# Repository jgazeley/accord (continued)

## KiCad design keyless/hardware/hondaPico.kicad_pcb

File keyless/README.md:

# Accord keyless

Pico W firmware and hardware for the keyless-entry module in a 2001 Honda
Accord. It provides BLE commands, proximity-based lock/unlock, automatic
relocking, and control of the trunk, lights and horn. It runs locally on the
board and retains USB/serial interfaces for diagnostics and control.

## Hardware

Open [hardware/hondaPico.kicad_pro](hardware/hondaPico.kicad_pro) in KiCad 9.
Install KiCad's standard symbol, footprint and 3D-model libraries. Project-local
custom symbols and footprints are included. The hardware project retains its
original `hondaPico` filename.

KiCad CLI 9.0.2 loads and exports the schematic and PCB. Checks report no errors,
but there are two schematic warnings, three board warnings and eight
PCB/schematic parity warnings. These include a missing J2 footprint and differing
R14/R15 values. See the [validation report](validation/kicad-20261027/README.md)
before using the design for fabrication. The 3D appearance has not been verified.

## Build

Use Arduino CLI 1.4.1 with Earle Philhower's Arduino-Pico core 6.1.0.
From `keyless/`:

```sh
arduino-cli compile --fqbn rp2040:rp2040:rpipicow:ipbtstack=ipv4btcble --build-path /tmp/accord-keyless-build firmware/accord-keyless
```

The board option enables BLE. The sketch is
[accord-keyless.ino](firmware/accord-keyless/accord-keyless.ino); it does not
require a Wi-Fi credential header. The existing BLE advertised name and
protocol names are unchanged.

## Tests

From `keyless/`, compile and run each native test:

```sh
for test in interlock relock proximity_act; do
  cc -std=c11 -Wall -Wextra -Werror "tests/${test}_test.c" -o "/tmp/accord-keyless-${test}" || exit
  "/tmp/accord-keyless-${test}" || exit
done
```

All three tests pass. The interlock and relock tests exercise copies of firmware
logic; they do not replace board testing or in-car proximity calibration.

Source provenance and validation are recorded in
[SOURCE_MANIFEST.json](SOURCE_MANIFEST.json).

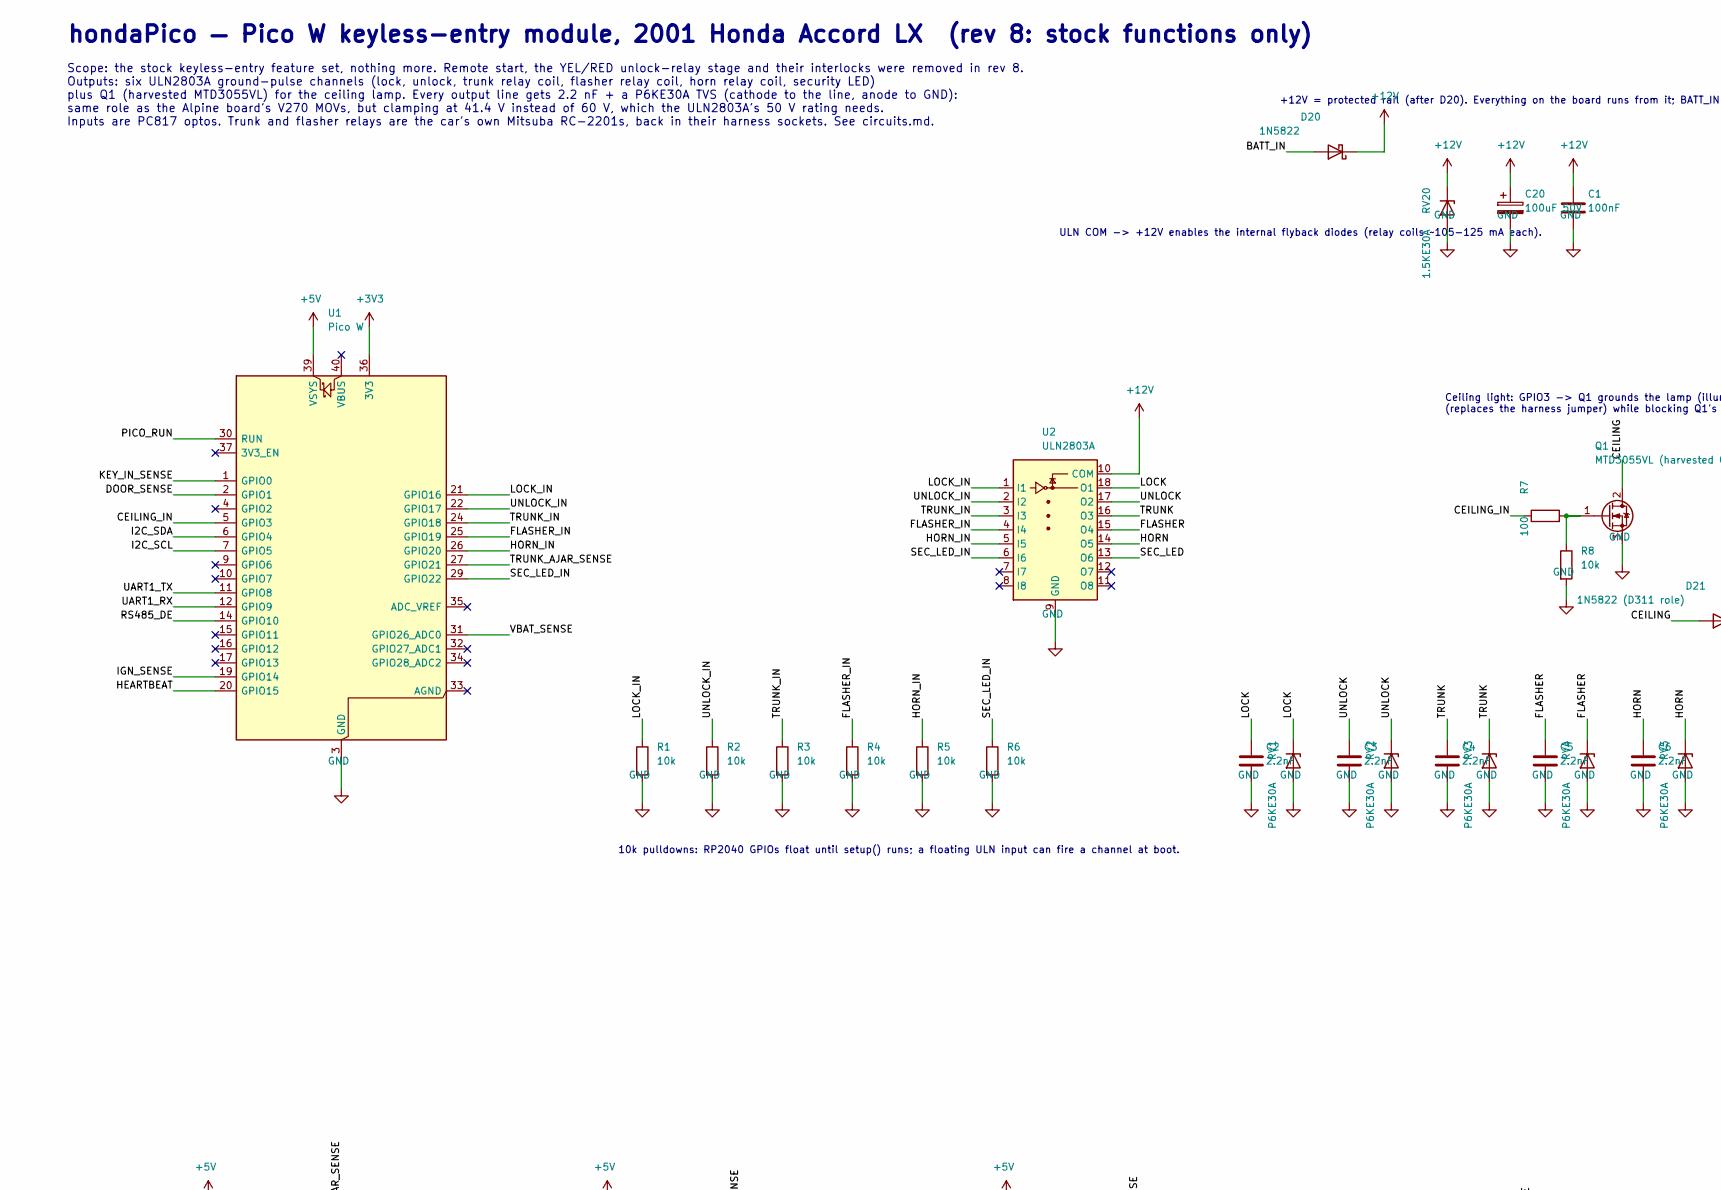
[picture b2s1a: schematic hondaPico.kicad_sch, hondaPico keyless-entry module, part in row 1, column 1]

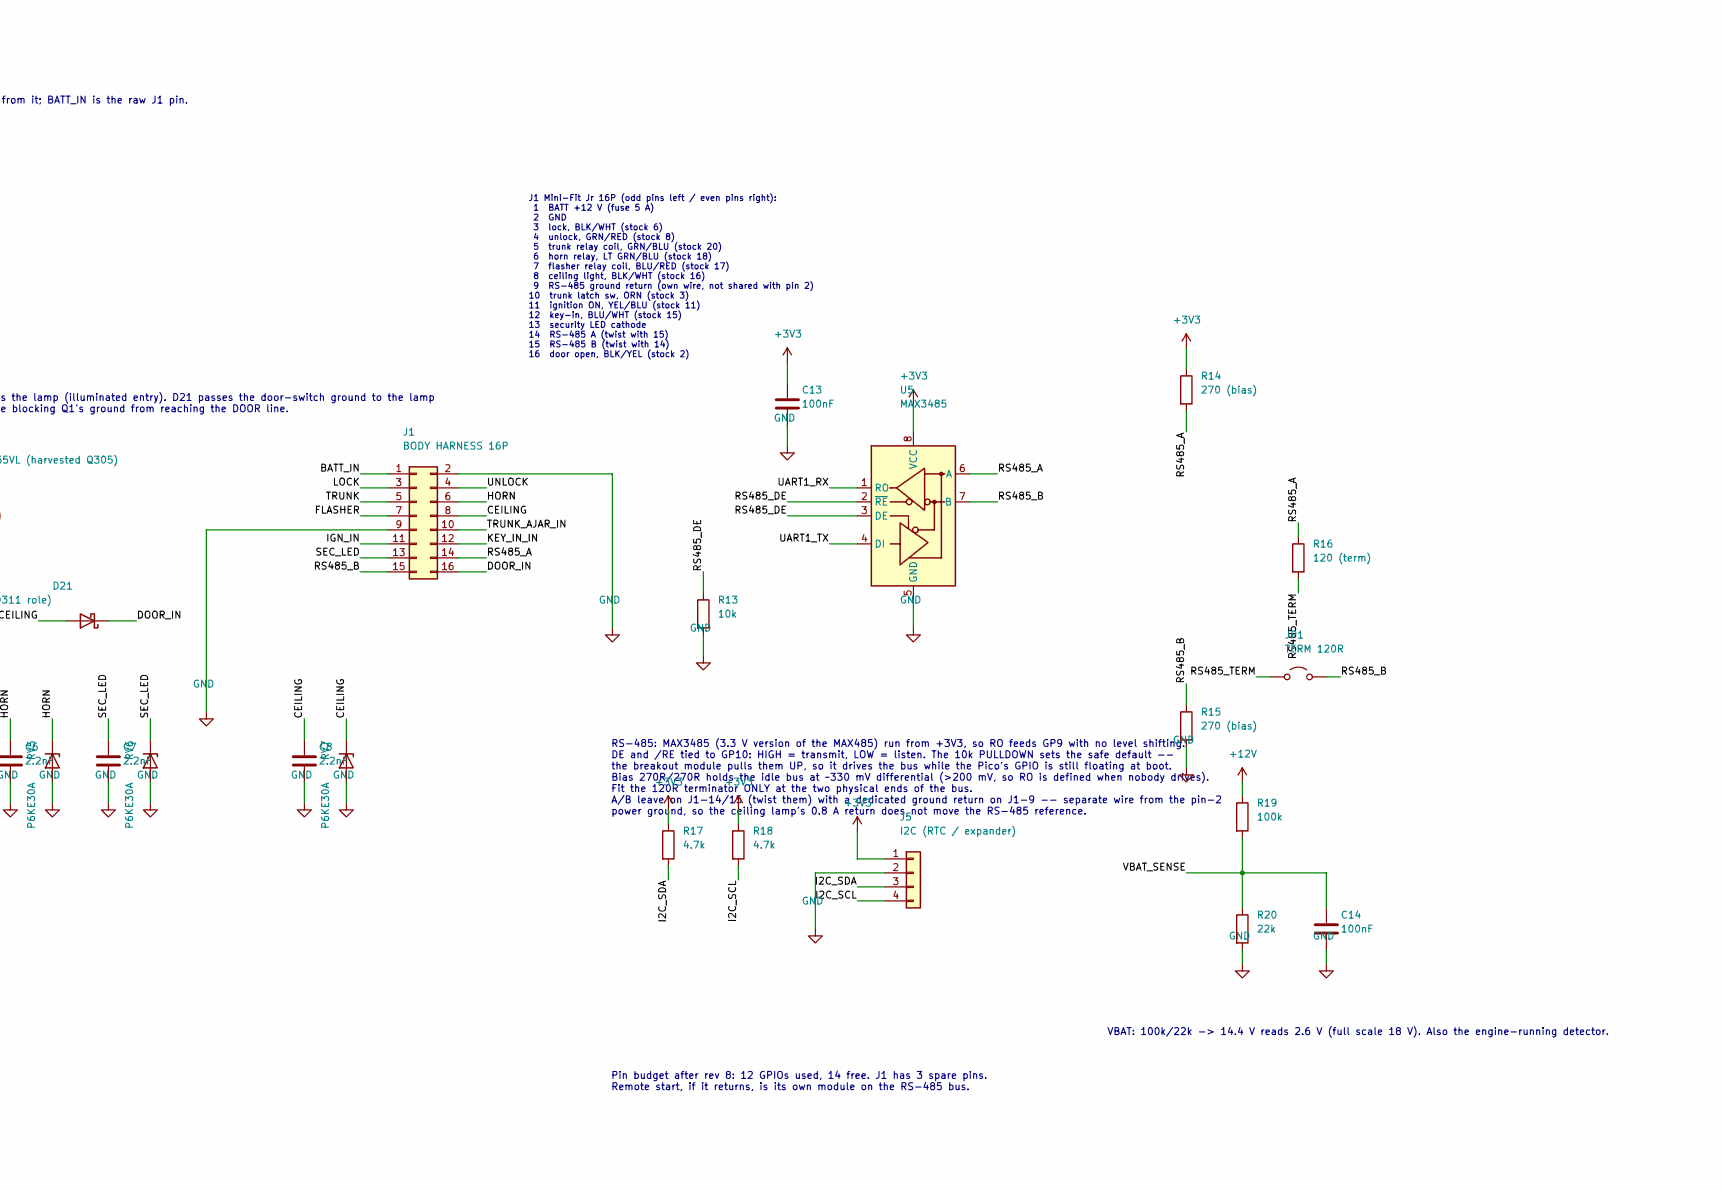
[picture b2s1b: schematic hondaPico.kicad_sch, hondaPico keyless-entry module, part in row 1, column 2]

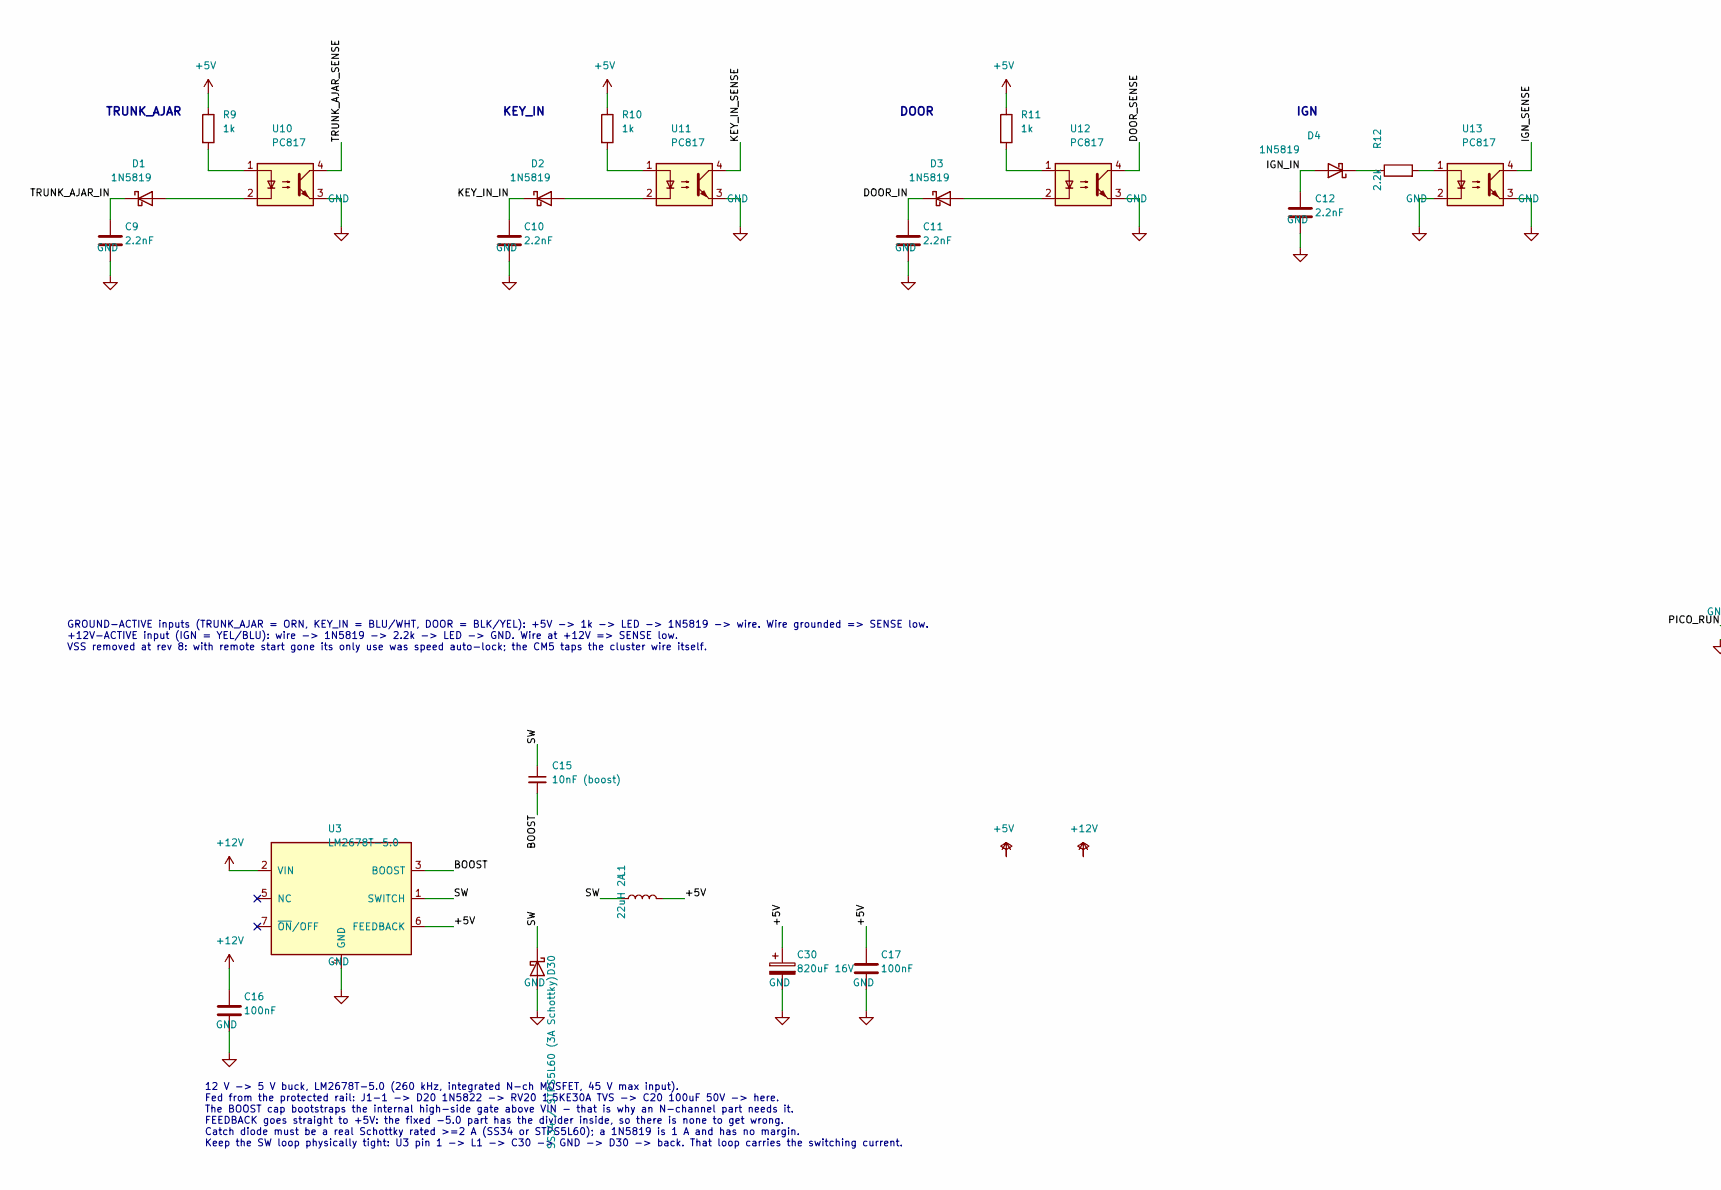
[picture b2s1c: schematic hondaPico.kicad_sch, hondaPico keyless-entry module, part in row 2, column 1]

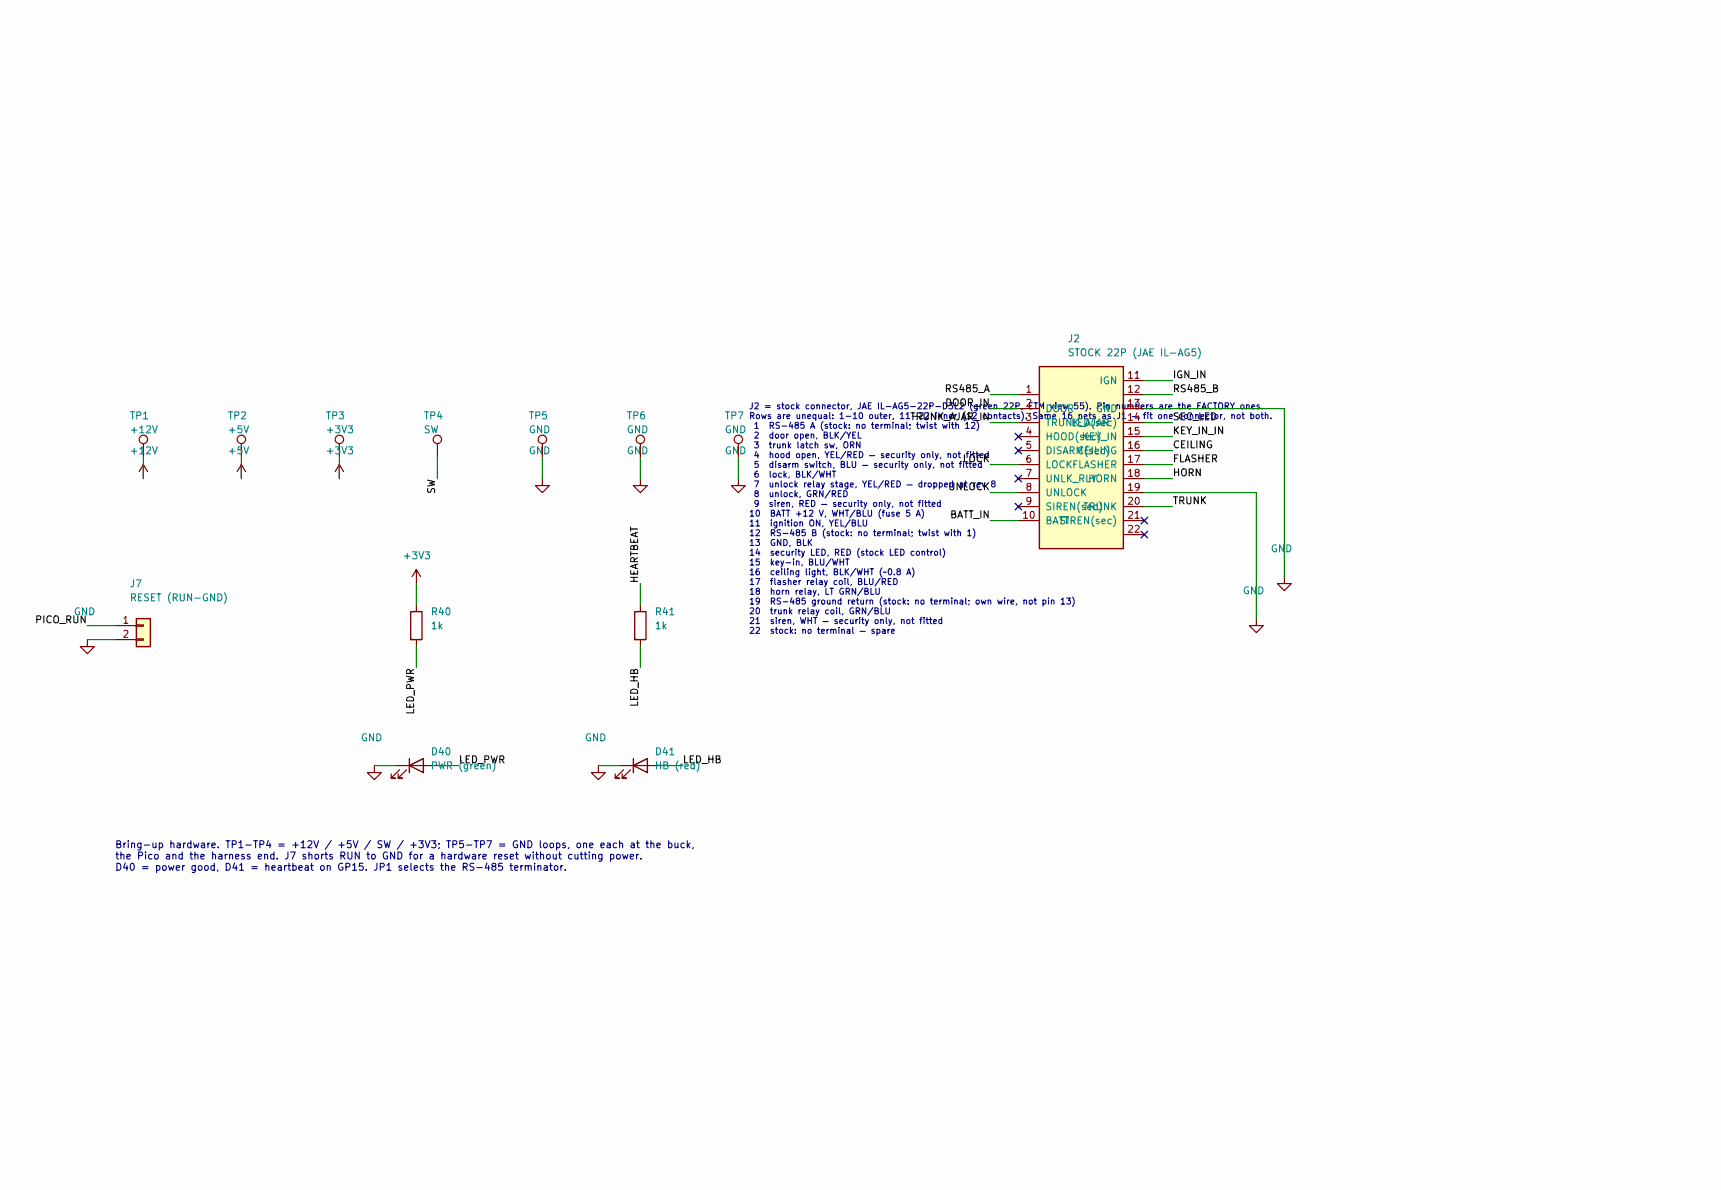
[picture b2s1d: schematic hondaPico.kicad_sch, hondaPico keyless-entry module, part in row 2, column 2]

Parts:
C1, C13, C14, C16, C17: 100nF; C_0805_2012Metric_Pad1.18x1.45mm_HandSolder
C2, C3, C4, C5, C6, C7, C8, C9, C10, C11, C12: 2.2nF; C_0805_2012Metric_Pad1.18x1.45mm_HandSolder
C15: 10nF (boost); C_Disc_D7.5mm_W5.0mm_P5.00mm
C20: 100uF 50V; CP_Radial_D8.0mm_P3.50mm
C30: 820uF 16V; CP_Radial_D10.0mm_P5.00mm
D1, D2, D3, D4: 1N5819; D_DO-41_SOD81_P5.08mm_Vertical_AnodeUp
D20: 1N5822; D_DO-201AD_P5.08mm_Vertical_AnodeUp
D21: 1N5822 (D311 role); D_DO-201AD_P5.08mm_Vertical_AnodeUp
D30: SS34 / STPS5L60 (3A Schottky); D_DO-201AD_P5.08mm_Vertical_AnodeUp
D40: PWR (green); LED_D3.0mm
D41: HB (red); LED_D3.0mm
J1: BODY HARNESS 16P; Molex_Mini-Fit_Jr_5569-16A2_2x08_P4.20mm_Horizontal
J2: STOCK 22P (JAE IL-AG5); JAE_IL-AG5-22P-D3L2
J5: I2C (RTC / expander); PinHeader_1x04_P2.54mm_Vertical
J7: RESET (RUN-GND); PinHeader_1x02_P2.54mm_Vertical
JP1: TERM 120R; PinHeader_1x02_P2.54mm_Vertical
L1: 22uH 2A; L_Radial_D10.0mm_P5.00mm_Fastron_07P
Q1: MTD3055VL (harvested Q305); TO-252-2
R1, R2, R3, R4, R5, R6, R8, R13: 10k; R_Axial_DIN0207_L6.3mm_D2.5mm_P5.08mm_Vertical
R7: 100; R_Axial_DIN0207_L6.3mm_D2.5mm_P5.08mm_Vertical
R9, R10, R11, R40, R41: 1k; R_Axial_DIN0207_L6.3mm_D2.5mm_P5.08mm_Vertical
R12: 2.2k; R_Axial_DIN0207_L6.3mm_D2.5mm_P5.08mm_Vertical
R14, R15: 270 (bias); R_Axial_DIN0207_L6.3mm_D2.5mm_P5.08mm_Vertical
R16: 120 (term); R_Axial_DIN0207_L6.3mm_D2.5mm_P5.08mm_Vertical
R17, R18: 4.7k; R_Axial_DIN0207_L6.3mm_D2.5mm_P5.08mm_Vertical
R19: 100k; R_Axial_DIN0207_L6.3mm_D2.5mm_P5.08mm_Vertical
R20: 22k; R_Axial_DIN0207_L6.3mm_D2.5mm_P5.08mm_Vertical
RV1, RV2, RV3, RV4, RV5, RV6, RV7: P6KE30A; D_DO-15_P5.08mm_Vertical_KathodeUp
RV20: 1.5KE30A; D_DO-201AD_P5.08mm_Vertical_KathodeUp
TP1: +12V; TestPoint_Loop_D2.50mm_Drill1.0mm
TP2: +5V; TestPoint_Loop_D2.50mm_Drill1.0mm
TP3: +3V3; TestPoint_Loop_D2.50mm_Drill1.0mm
TP4: SW; TestPoint_Loop_D2.50mm_Drill1.0mm
TP5, TP6, TP7: GND; TestPoint_Loop_D2.50mm_Drill1.0mm
U1: Pico W; RaspberryPi_Pico_Common_SMD
U2: ULN2803A; DIP-18_W7.62mm
U3: LM2678T-5.0; TO-220-7_P2.54x3.7mm_StaggerOdd_Lead3.8mm_Vertical
U5: MAX3485; DIP-8_W7.62mm
U10, U11, U12, U13: PC817; DIP-4_W7.62mm

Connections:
+3V3: C13.1, J5.1, R14.1, R17.1, R18.1, R40.1, TP3.1, U1.36 (3V3), U5.8 (VCC)
+5V: C17.1, C30.1, L1.2, R9.1, R10.1, R11.1, TP2.1, U1.39 (VSYS), U3.6 (FEEDBACK)
+12V: C1.1, C16.1, C20.1, D20.1 (K), R19.1, RV20.1 (K), TP1.1, U2.10 (COM), U3.2 (VIN)
/BATT_IN: D20.2 (A), J1.1, J2.10 (BATT)
/BOOST: C15.2, U3.3 (BOOST)
/CEILING: C8.1, D21.2 (A), J1.8, J2.16 (CEILING), Q1.2 (D), RV7.1 (K)
/CEILING_IN: R7.1, U1.5 (GPIO3)
/DOOR_IN: C11.1, D3.1 (K), D21.1 (K), J1.16, J2.2 (DOOR)
/DOOR_SENSE: U1.2 (GPIO1), U12.4
/FLASHER: C5.1, J1.7, J2.17 (FLASHER), RV4.1 (K), U2.15 (O4)
/FLASHER_IN: R4.1, U1.25 (GPIO19), U2.4 (I4)
/HEARTBEAT: R41.1, U1.20 (GPIO15)
/HORN: C6.1, J1.6, J2.18 (HORN), RV5.1 (K), U2.14 (O5)
/HORN_IN: R5.1, U1.26 (GPIO20), U2.5 (I5)
/I2C_SCL: J5.4, R18.2, U1.7 (GPIO5)
/I2C_SDA: J5.3, R17.2, U1.6 (GPIO4)
/IGN_IN: C12.1, D4.2 (A), J1.11, J2.11 (IGN)
/IGN_SENSE: U1.19 (GPIO14), U13.4
/KEY_IN_IN: C10.1, D2.1 (K), J1.12, J2.15 (KEY_IN)
/KEY_IN_SENSE: U1.1 (GPIO0), U11.4
/LED_HB: D41.2 (A), R41.2
/LED_PWR: D40.2 (A), R40.2
/LOCK: C2.1, J1.3, J2.6 (LOCK), RV1.1 (K), U2.18 (O1)
/LOCK_IN: R1.1, U1.21 (GPIO16), U2.1 (I1)
/PICO_RUN: J7.1, U1.30 (RUN)
/RS485_A: J1.14, J2.1, R14.2, R16.1, U5.6 (A)
/RS485_B: J1.15, J2.12, JP1.2 (B), R15.1, U5.7 (B)
/RS485_DE: R13.1, U1.14 (GPIO10), U5.2 (~RE), U5.3 (DE)
/RS485_TERM: JP1.1 (A), R16.2
/SEC_LED: C7.1, J1.13, J2.14 (LED(sec)), RV6.1 (K), U2.13 (O6)
/SEC_LED_IN: R6.1, U1.29 (GPIO22), U2.6 (I6)
/SW: C15.1, D30.1 (K), L1.1, TP4.1, U3.1 (SWITCH)
/TRUNK: C4.1, J1.5, J2.20 (TRUNK), RV3.1 (K), U2.16 (O3)
/TRUNK_AJAR_IN: C9.1, D1.1 (K), J1.10, J2.3 (TRUNK_AJAR)
/TRUNK_AJAR_SENSE: U1.27 (GPIO21), U10.4
/TRUNK_IN: R3.1, U1.24 (GPIO18), U2.3 (I3)
/UART1_RX: U1.12 (GPIO9), U5.1 (RO)
/UART1_TX: U1.11 (GPIO8), U5.4 (DI)
/UNLOCK: C3.1, J1.4, J2.8 (UNLOCK), RV2.1 (K), U2.17 (O2)
/UNLOCK_IN: R2.1, U1.22 (GPIO17), U2.2 (I2)
/VBAT_SENSE: C14.1, R19.2, R20.1, U1.31 (GPIO26_ADC0)
GND: C1.2, C2.2, C3.2, C4.2, C5.2, C6.2, C7.2, C8.2, C9.2, C10.2, C11.2, C12.2, C13.2, C14.2, C16.2, C17.2, C20.2, C30.2, D30.2 (A), D40.1 (K), D41.1 (K), J1.2, J1.9, J2.13 (GND), J2.19, J5.2, J7.2, Q1.3 (S), R1.2, R2.2, R3.2, R4.2, R5.2, R6.2, R8.2, R13.2, R15.2, R20.2, RV1.2 (A), RV2.2 (A), RV3.2 (A), RV4.2 (A), RV5.2 (A), RV6.2 (A), RV7.2 (A), RV20.2 (A), TP5.1, TP6.1, TP7.1, U1.3 (GND), U1.8 (GND), U1.13 (GND), U1.18 (GND), U1.23 (GND), U1.28 (GND), U1.38 (GND), U2.9 (GND), U3.4 (GND), U5.5 (GND), U10.3, U11.3, U12.3, U13.2, U13.3
unnamed: D1.2 (A), U10.2
unnamed: D2.2 (A), U11.2
unnamed: D3.2 (A), U12.2
unnamed: D4.1 (K), R12.1
unnamed: Q1.1 (G), R7.2, R8.1
unnamed: R9.2, U10.1
unnamed: R10.2, U11.1
unnamed: R11.2, U12.1
unnamed: R12.2, U13.1

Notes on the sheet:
+12V = protected rail (after D20). Everything on the board runs from it; BATT_IN is the raw J1 pin.
Ceiling light: GPIO3 -> Q1 grounds the lamp (illuminated entry). D21 passes the door-switch ground to the lamp (replaces the harness jumper) while blocking Q1's ground from reaching the DOOR line.
J1 Mini-Fit Jr 16P (odd pins left / even pins right): 1 BATT +12 V (fuse 5 A) 2 GND 3 lock, BLK/WHT (stock 6) 4 unlock, GRN/RED (stock 8) 5 trunk relay coil, GRN/BLU (stock 20) 6 horn relay, LT GRN/BLU (stock 18) 7 flasher relay coil, BLU/RED (stock 17) 8 ceiling light, BLK/WHT (stock 16) 9 RS-485 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
J2 = stock connector, JAE IL-AG5-22P-D3L2 (green 22P, ETM view 55). Pin numbers are the FACTORY ones. Rows are unequal: 1-10 outer, 11-22 inner (12 contacts). Same 16 nets as J1 — fit one connector, not both. 1 RS-485 A (stock: no terminal; twist with 12) 2 door open, BLK/YEL 3 trunk latch sw, ORN 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
TRUNK_AJAR
KEY_IN
DOOR
IGN
RS-485: MAX3485 (3.3 V version of the MAX485) run from +3V3, so RO feeds GP9 with no level shifting. DE and /RE tied to GP10: HIGH = transmit, LOW = listen. The 10k PULLDOWN sets the safe default -- the breakout module pulls them UP, so it drives the bus while the Pico's GPIO is still floating at b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
Bring-up hardware. TP1-TP4 = +12V / +5V / SW / +3V3; TP5-TP7 = GND loops, one each at the buck, the Pico and the harness end. J7 shorts RUN to GND for a hardware reset without cutting power. D40 = power good, D41 = heartbeat on GP15. JP1 selects the RS-485 terminator.
12 V -> 5 V buck, LM2678T-5.0 (260 kHz, integrated N-ch MOSFET, 45 V max input). Fed from the protected rail: J1-1 -> D20 1N5822 -> RV20 1.5KE30A TVS -> C20 100uF 50V -> here. The BOOST cap bootstraps the internal high-side gate above VIN - that is why an N-channel part needs it. FEEDBACK goes stra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
hondaPico — Pico W keyless-entry module, 2001 Honda Accord LX (rev 8: stock functions only)
Scope: the stock keyless-entry feature set, nothing more. Remote start, the YEL/RED unlock-relay stage and their interlocks were removed in rev 8. Outputs: six ULN2803A ground-pulse channels (lock, unlock, trunk relay coil, flasher relay coil, horn relay coil, security LED) plus Q1 (harvested MTD30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
10k pulldowns: RP2040 GPIOs float until setup() runs; a floating ULN input can fire a channel at boot.
ULN COM -> +12V enables the internal flyback diodes (relay coils ~105-125 mA each).
GROUND-ACTIVE inputs (TRUNK_AJAR = ORN, KEY_IN = BLU/WHT, DOOR = BLK/YEL): +5V -> 1k -> LED -> 1N5819 -> wire. Wire grounded => SENSE low. +12V-ACTIVE input (IGN = YEL/BLU): wire -> 1N5819 -> 2.2k -> LED -> GND. Wire at +12V => SENSE low. VSS removed at rev 8: with remote start gone its only use wa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
VBAT: 100k/22k -> 14.4 V reads 2.6 V (full scale 18 V). Also the engine-running detector.
Pin budget after rev 8: 12 GPIOs used, 14 free. J1 has 3 spare pins. Remote start, if it returns, is its own module on the RS-485 bus.

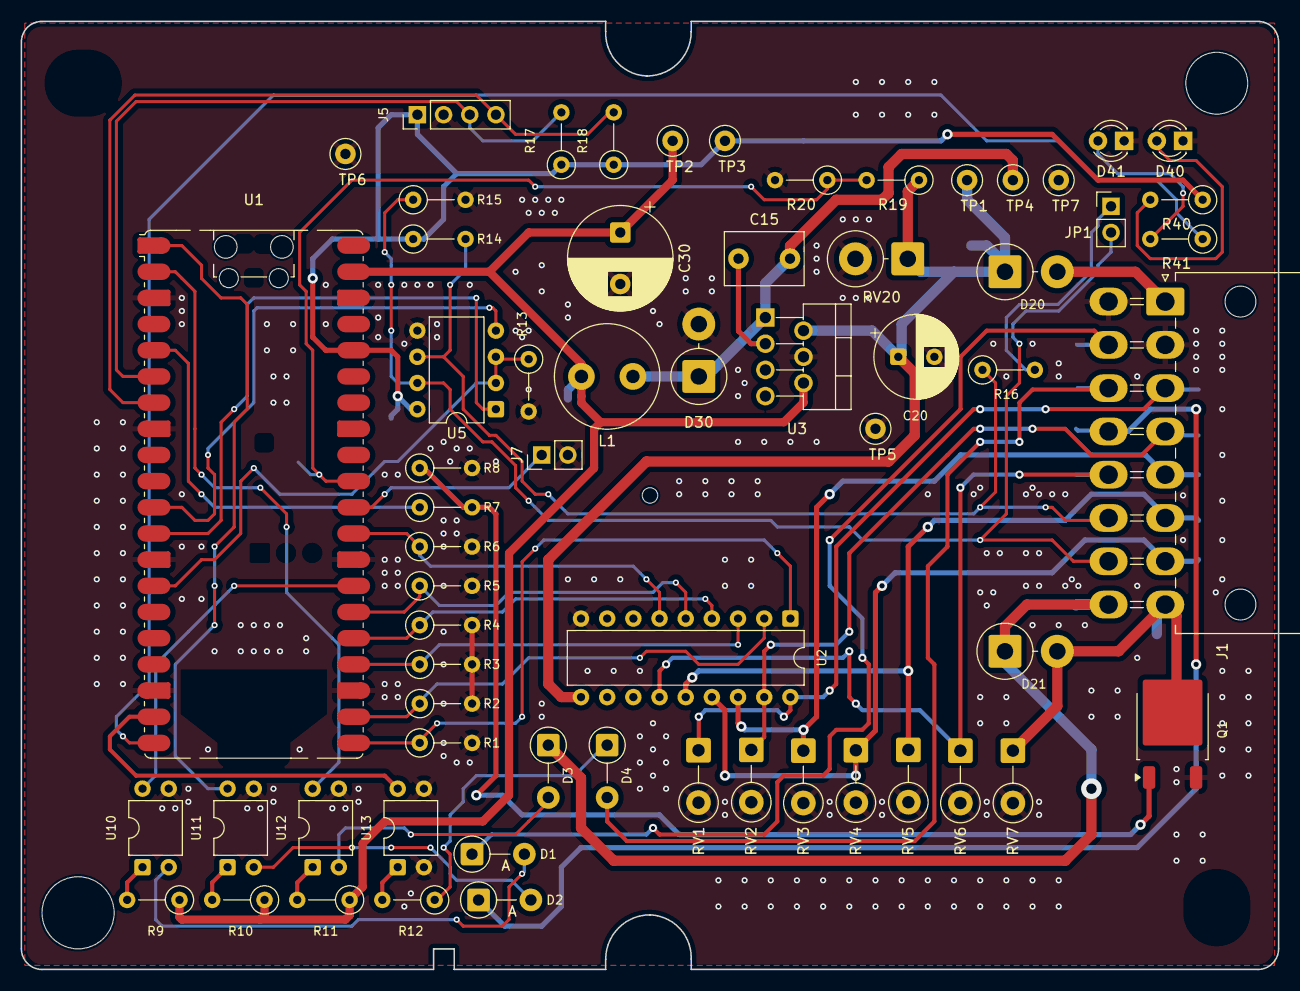
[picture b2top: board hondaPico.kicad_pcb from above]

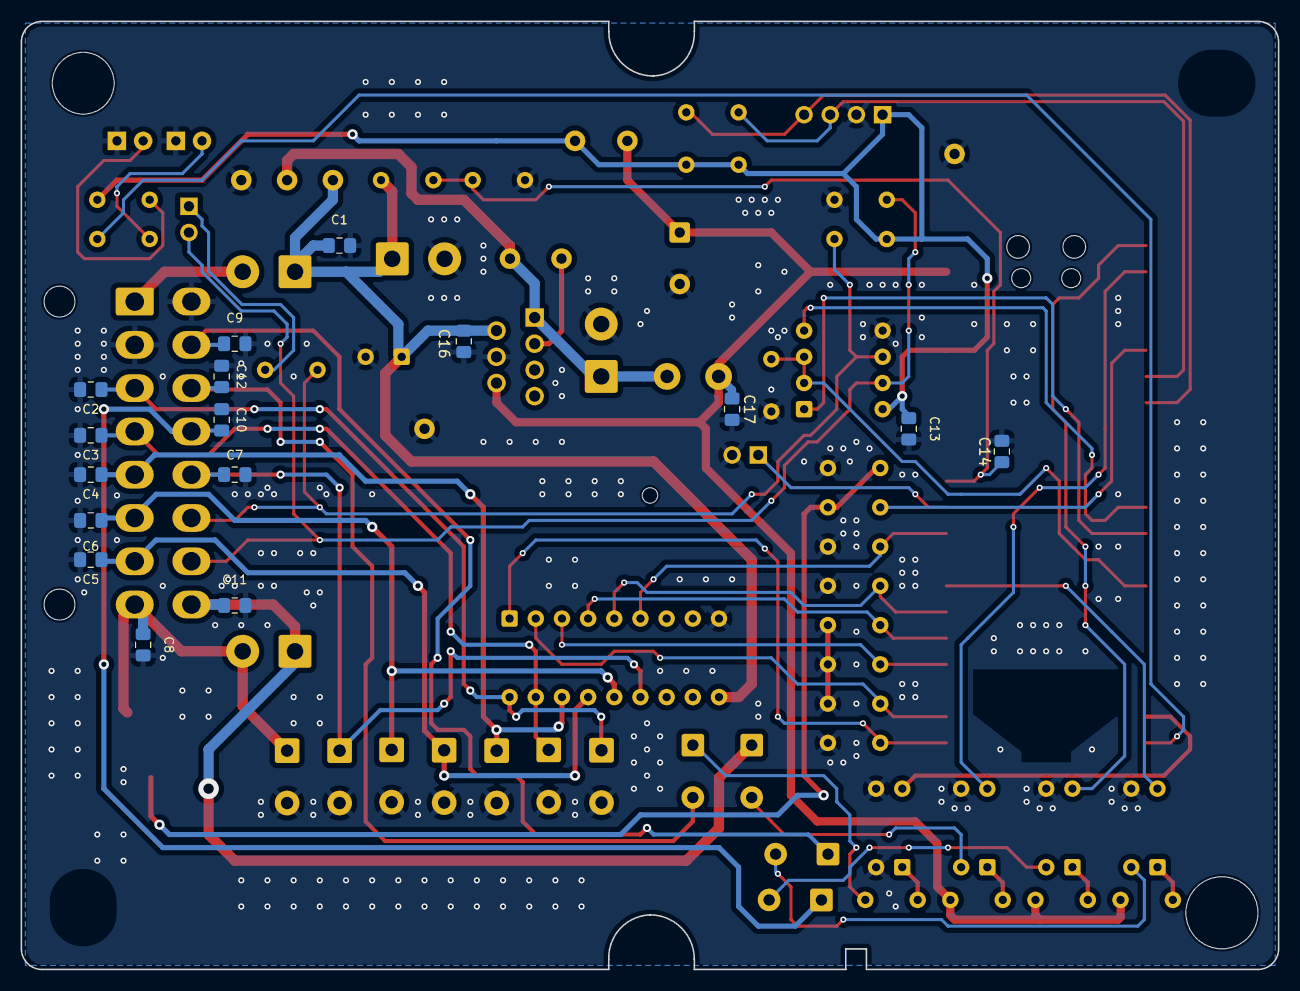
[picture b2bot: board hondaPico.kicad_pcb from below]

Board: 2 copper layers, 122.0 x 92.0 mm, 84 parts (16 on the bottom side), 51 nets.

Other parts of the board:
H1, H2, H3, H4, H5: ENCLOSURE POST

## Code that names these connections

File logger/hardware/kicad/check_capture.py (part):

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    check(f'U1 pin {pin} ({label}) unconnected', unconnected('U1', pin),
          f'on net {pin_net.get(("U1", pin))!r}')
for pin in ('3', '8', '13', '18', '23', '28', '38'):
    check(f'U1 pin {pin} GND -> PGND', pin_net.get(('U1', pin)) == 'PGND',
          f'got {pin_net.get(("U1", pin))!r}')

# No rail but switched 3V3 may be tied to a GPIO net through a resistor.
GPIO_NETS = set(PINMAP.values()) - {'PGND', 'AGND', 'P3V3_SW', 'VSYS'}
for r in bom:
    if not r['symbol'].startswith('Device:R'):
        continue
    ends = {pin_net.get((r['reference'], '1')),
            pin_net.get((r['reference'], '2'))}
    if ends & GPIO_NETS and ends & {'A5', 'B5', 'P12', 'P_AON', 'VCLK'}:
        check(f'{r["reference"]} does not tie a GPIO to a non-3V3 rail',
              False, f'between {sorted(x for x in ends if x)}')
checks += 1        # the absence of any such part is itself one check
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    value(f'C_{key}', '1uF')
    check(f'{key} upper clamp anode at the pin',
          pin_net.get((R(f'D_{key}_H'), '2')) == adc
          and pin_net.get((R(f'D_{key}_H'), '1')) == 'P3V3_SW',
          'upper clamp orientation wrong')
    check(f'{key} lower clamp cathode at the pin',
          pin_net.get((R(f'D_{key}_L'), '1')) == adc
          and pin_net.get((R(f'D_{key}_L'), '2')) == 'AGND',
          'lower clamp orientation wrong')
for key, sig in (('VSS', 'VSS_IN'), ('TACH', 'TACH_IN'), ('BRK', 'BRAKE_IN')):
    check(f'{key} clamp anode at the pin',
          pin_net.get((R(f'D_{key}'), '2')) == sig
          and pin_net.get((R(f'D_{key}'), '1')) == 'P3V3_SW',
          'clamp orientation wrong')

# -------------------------------------- X1 resolved: the B2 series isolation
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      'an always-on rail here would leave B2 connected while parked, which '
      'is the fault this part exists to remove')
check('both enable gates are pulled down, so the relay is open by default',
      pin_net.get((R('R_ISOEN_PD'), '2')) == 'PGND'
      and pin_net.get((R('R_ISOPG_PD'), '2')) == 'PGND')

# ------------------- X2-X5: the four branches decided as a justified bypass
# Positive assertion of the decision: each tap reaches its divider top
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value('RLED', '2.2k')
wires('opto cell', 'U2', {1: 'IGN_LED_A', 2: 'PGND', 3: 'IGN_A', 4: 'A5'})
check('the opto LED cathode returns to PGND, not to the B16 conductor',
      pin_net.get(('U2', '2')) == 'PGND'
      and pin_net.get(('U2', '2')) != pin_net.get(('J1', '10')),
      'R06-REV-2: B16 is a reference and must never carry the LED current')
check('no capacitor sits across the old opto output node',
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check('no fuse is fitted on the board (D-FUSE-10: harness inline fuse)',
      not any(r['symbol'] == 'Device:Fuse' for r in bom))
check('BATT_IN runs straight from J1 to the reverse-block diode',
      sorted(n for n, net in pin_net.items() if net == 'BATT_IN')
      == sorted([('J1', '6'), (R('DREV'), '2')]))
check('the onboard ignition fuse is not fitted',
      'FIGN' not in by_src,
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      pin_net.get(('U2', '4')) != pin_net.get(('U1', '7')),
      'the old raw-GP5 arrangement would violate D-RA-03')
check('the opto reverse clamp is antiparallel with the LED',
      pin_net.get((R('DR'), '1')) == 'IGN_LED_A'
      and pin_net.get((R('DR'), '2')) == 'PGND',
      'with the cathode on PGND the clamp has to share both nodes')

# ---------------------------------------- X6 resolved: qualified ignition
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     'nothing else may load or feed the report node')
check('the report node carries no capacitor, so its delay is not an unknown',
      not any(r['symbol'].startswith('Device:C')
              and 'QUAL_N_REPORT' in (pin_net.get((r['reference'], '1')),
                                      pin_net.get((r['reference'], '2')))
              for r in bom),
      'D1 asks for the report delay to sit inside the 10 ms budget; with no '
      'capacitor it is the pullup against node capacitance alone')
check('IGN_RC rises for ON: the filter charges through RRC from IGN_A',
      pin_net.get((R('RRC'), '1')) == 'IGN_A',
      'an empty capacitor must mean OFF (CUTOFF_MARGIN_REVIEW S2)')

# ---------------------------------- X7 second stage and the A5 rail
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      unconnected(R('UA5'), '3'),
      'its absolute maximum is 7 V; it must never be tied to a rail')
check('the A5 regulator is fed through the second stage, not from P12',
      pin_net.get((R('UA5'), '1')) == 'P_AON',
      'the <=28 V protected-rail criterion is met at P_AON')
for ref in ('C_A5A', 'C_A5B'):
    wires('A5 output capacitance', ref, {1: 'A5', 2: 'PGND'})
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wires('clock', 'UGCLK', {1: 'PGND', 2: 'PGND', 3: 'XO_OUT', 4: 'CLK32',
                         5: 'A5', 6: 'ARM'})
check('the oscillator enable buffer runs from the filtered rail, not A5',
      pin_net.get((R('UOE'), '5')) == 'VCLK',
      'it must not inject A5 into the oscillator enable pin')
only('XO_OUT', [('UXO', 1), ('UGCLK', 3)],
     'total XO_OUT load must stay inside 10 pF, so nothing else sits here')
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wires('counter', 'UCOUNT', {16: 'A5', 8: 'PGND', 10: 'UCLK_Q14',
                            11: 'BASE_RESET', 2: 'CNT_Q13', 13: 'CNT_Q8'})
check('UCOUNT is not reset by NARM',
      pin_net.get((R('UCOUNT'), '11')) == 'BASE_RESET',
      'resetting it from NARM would erase EXPIRED as it disarmed the latch')
wires('latch', 'ULATCH', {1: 'SET_N', 2: 'NARM', 3: 'ARM', 4: 'NARM',
                          5: 'RESET_N', 6: 'ARM', 7: 'PGND', 8: 'QUAL_N',
                          9: 'QUAL_N', 10: 'IGN_Q', 12: 'PGND', 13: 'PGND',
                          14: 'A5'})
check('the unused latch gate has its inputs tied to a rail',
      pin_net.get((R('ULATCH'), '12')) == 'PGND'
      and pin_net.get((R('ULATCH'), '13')) == 'PGND',
      'a floating CMOS input draws current and can oscillate')
check('the unused latch gate output is left open',
      unconnected(R('ULATCH'), '11'))
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wires('permission switch', 'R_QSG', {1: 'ARM', 2: 'ARM_G'})
wires('permission switch', 'R_QSPD', {1: 'ARM_G', 2: 'PGND'})
check('QS is in series between SINK and the QH collector',
      pin_net.get((R('QH'), '3')) == 'QH_C'
      and pin_net.get((R('QS'), '2')) == 'QH_C'
      and pin_net.get((R('QS'), '3')) == 'SINK',
      'capture question Q6: the inhibit has to interrupt the HOLD sink path')
only('QH_C', [('QH', 3), ('QS', 2)],
     'nothing may bridge the permission switch')
check('QI still sinks directly, so raw ignition overrides the cutoff',
      pin_net.get((R('QI'), '3')) == 'SINK')
check('QH keeps its emitter grounded',
      by_role('QH', 'E') == 'PGND',
      'interrupting the emitter would couple fault voltage into HOLD')
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wires('HOLD sense', 'R_MONPD', {1: 'MON_B', 2: 'PGND'})
wires('HOLD sense', 'R_MONC', {1: 'HOLD_N', 2: 'A5'})
check('QMON senses HOLD_RAW ahead of the JH maintenance link',
      pin_net.get((R('R_MONB'), '1')) == 'HOLD_RAW',
      'opening JH must release QH without blinding the monitor')
check('the A5 pullup stays on HOLD_N, not on the GPIO',
      {pin_net.get((R('R_MONC'), '1')),
       pin_net.get((R('R_MONC'), '2'))} == {'HOLD_N', 'A5'})

# the cutoff-period selection: exactly one link, clearly distinguished
wires('period select', 'R_EXPP', {1: 'CNT_Q13', 2: 'EXPIRED'})
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      sum(1 for s in ('R_EXPP', 'R_EXPT')
          if by_src[s]['population'] == 'FIT') == 1)
check('EXPIRED cannot float with neither link fitted',
      pin_net.get((R('R_EXP'), '2')) == 'PGND')
check('the maintenance HOLD link and the period select are different things',
      by_src['JH']['value'] == 'HOLD link'
      and by_src['R_EXPP']['value'] == '0R')
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wires('HOLD driver', 'RBH', {1: 'HOLD_B', 2: 'PGND'})

# --------------------------------------------------------- SD, delta D6
check('SD module is on switched 3V3', pin_net.get(('J5', '1')) == 'P3V3_SW')
wires('SD bulk', 'C_SD', {1: 'P3V3_SW', 2: 'PGND'})
check('the SD bulk value is selected, not a range',
      by_src['C_SD']['value'] == '47uF/16V',
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      'Connector_PinHeader_2.54mm:PinHeader_2x03_P2.54mm_Vertical')
wires('RS485 default listen', 'R_DE', {1:'BUS_DE',2:'PGND'})
value('R_DE','10k')
wires('keyless U5 pin map', 'U485', {1:'UART1_RX',2:'BUS_DE',3:'BUS_DE',
      4:'UART1_TX',5:'PGND',6:'RS485_A',7:'RS485_B',8:'P3V3_SW'})
wires('RS485 decoupling', 'C485', {1:'P3V3_SW',2:'PGND'})
wires('RS485 high bias', 'R485_A', {1:'RS485_BIAS_HI',2:'RS485_A'})
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    check(src+' matches keyless JP1 footprint',by_src[src]['footprint']==
          'Connector_PinHeader_2.54mm:PinHeader_1x02_P2.54mm_Vertical')
# ------------------------ J1, the single board connector (D-CONN-06)
J1_PINS = {1: 'RS485_A', 2: 'PGND', 3: 'B2_TAP', 4: 'B1_TAP', 5: 'B11_TAP',
           6: 'BATT_IN', 7: 'RS485_B', 9: 'C11_TAP', 10: 'AGND',
           13: 'C14_TAP', 14: 'PGND'}
J1_SPARE = (8, 11, 12)
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    (ax, ay), (bx, by) = _face(a), _face(b)
    return ((ax - bx) ** 2 + (ay - by) ** 2) ** 0.5 <= r
_all = {**J1_PINS, **{p: 'spare' for p in J1_SPARE}}
_batt = [p for p, n in J1_PINS.items() if n == 'BATT_IN'][0]
_batt_nb = {_all[n] for n in _pads if n != _batt and _near(_batt, n)}
check('BATT_IN\'s neighbours are only grounds and 12 V-level inputs',
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
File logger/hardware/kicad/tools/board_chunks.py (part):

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     'U15 pins 6/7 (A/B)'),
    ('A  Pico peripherals', 'headers', 'J3 J4',
     'J3 2x03 spare header (GP11-13 + switched power) by Pico pins 15-17; '
     'J4 RUN-GND reset by pin 30'),
    ('A  Pico peripherals', 'power_tps', 'TP1 TP2 TP3 TP4 TP5 TP6 TP7 TP21 '
     'TP22 TP23',
     'test points on the placed power block: P12, GATE, VIN_SW, SW, B5, '
     'VSYS, 3V3, two PGND, AGND. Each beside the part that makes its net; '
     'AGND near Pico pin 33'),

    ('B  vehicle inputs', 'in_tach', 'R3 R4 D102',
     'B1 tach: J1.4 -> R3 22k -> GP3 (pin 5), R4 6.8k to PGND, D102 clamp '
     'to 3V3 at the Pico pin'),
    ('B  vehicle inputs', 'in_brake', 'R5 R6 D103',
     'C14 brake: J1.13 -> R5 22k -> GP4 (pin 6), R6 6.8k to PGND, D103 '
     'clamp to 3V3 at the Pico pin'),
    ('B  vehicle inputs', 'in_fuel', 'R7 R8 R9 C1 D104 D105',
     'C11 fuel: J1.9 -> R7 7.5k / R8 4.7k -> R9 1k -> GP26 (pin 31); C1 and '
     'the D104/D105 clamps at the ADC pin; returns to AGND, not PGND'),
    ('B  vehicle inputs', 'in_supply', 'D108 R10 R11 R12 C2 D106 D107',
     'B11 supply sense: J1.5 -> D108 TVS right at J1 -> R10 22k / R11 4.7k '
     '-> R12 1k -> GP27 (pin 32); C2 and D106/D107 at the ADC pin; AGND '
     'returns'),
    ('B  vehicle inputs', 'in_vss', 'U3 R1 R2 D101',
     'B2 VSS: J1.3 -> U3 ASSR-601JV relay output -> R1 22k / R2 33k -> GP2 '
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    ('C  always-on 5 V and ignition', 'a5_reg', 'U4 C4 C5 C6 TP9',
     'TPS70950 always-on 5 V (A5): C4 at its input, C5/C6 at its output'),
    ('C  always-on 5 V and ignition', 'a5_supervisor', 'U5 C7 TP17',
     'TPS3839 supervisor on A5, makes PGOOD; C7 at its supply pin'),
    ('C  always-on 5 V and ignition', 'iso_enable', 'R23 Q3 Q4 R24 R25 R26 '
     'R27 TP20',
     'U3 relay LED driver: R23 270R from B5, Q3 (PGOOD) and Q4 (GP7, pin '
     '10) in series to PGND, with their gate resistors. Next to U3'),
    ('C  always-on 5 V and ignition', 'qual_rc', 'R14 R15 C3 TP12',
     'ignition filter on the opto output: R14 47k, R15 220k, C3 1 uF '
     '(IGN_A -> IGN_RC). Next to U2 pins 3/4'),
    ('C  always-on 5 V and ignition', 'qual_reset', 'Q1 R16 R17 R18',
     'QRESET discharges the ignition filter when BAD: Q1 and R16-R18, next '
     'to C3'),
    ('C  always-on 5 V and ignition', 'qual_report', 'Q2 R19 R20 R21',
     'QREPORT drives GP5 (pin 7) from IGN_Q: Q2 with R19/R20, R21 10k '
     'pull-up to 3V3 at the Pico pin'),

    ('D  power hold and cutoff timer', 'hold', 'JP1 R28 R29',
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     'oscillator enable buffer U8 (C17) and clock gate U9 (C18), beside U7'),
    ('D  power hold and cutoff timer', 'schmitt', 'U14 C23',
     'CD4093 Schmitt gates: conditions the ignition filter and PGOOD into '
     'IGN_Q / BAD. C23 at its supply pins. Near C3 and U5'),
    ('D  power hold and cutoff timer', 'latch', 'U12 C21',
     'CD4011 ARM latch, C21 at its supply pins. Beside U14'),
    ('D  power hold and cutoff timer', 'or_tree', 'U13 C22',
     'CD4071 reset OR tree, C22 at its supply pins. Beside U12'),
    ('D  power hold and cutoff timer', 'divider', 'U10 C19',
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
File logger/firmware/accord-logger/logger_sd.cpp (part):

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// SPI0, wired as built 2026-10-18 (SPEC 5.2). The module's own 3V3 pin is fed
// from the Pico's 3V3(OUT), so the shifter's rail cannot exceed 3.3 V whatever
// a card does -- that is what makes MISO on GP16 safe here.
constexpr uint8_t PIN_SD_MISO = 16, PIN_SD_CS = 17, PIN_SD_SCK = 18,
                  PIN_SD_MOSI = 19;
// 12 MHz, not the 25 MHz these cards will take: the signals cross a level
// shifter and jumper wires. Bandwidth is irrelevant here -- 1 Hz of 40-byte
// lines is 40 B/s against a 512-byte sector.
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    ++cardGeneration;
    syncedBytes = 0;
    if (uploadDir) uploadDir.close();
    if (!sd.begin(SdSpiConfig(PIN_SD_CS, SHARED_SPI, SD_SCK_MHZ(SD_CLOCK_MHZ),
                              &SPI))) {
        trackWorst(t0);
        /* The label alone cannot tell an empty slot from a dead bus: both set a
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}

void sdSetup() {
    SPI.setRX(PIN_SD_MISO);
    SPI.setCS(PIN_SD_CS);
    SPI.setSCK(PIN_SD_SCK);
    SPI.setTX(PIN_SD_MOSI);
    FsDateTime::setCallback(dateTimeCallback);
}

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
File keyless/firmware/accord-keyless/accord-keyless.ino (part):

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// banner scrolls away, and on a board in a car it is usually missed entirely.
// Declared up here because the status dump reads it well before setup() runs;
// arduino-cli hoists function prototypes but NOT variables.
const char* rs485Verdict = "not run";

#define PIN_TX    4
#define PIN_RX    5
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// D41 (red) on GP15 through R41. The real liveness indicator: it proves the
// sketch is running even when no link is connected. LED_BUILTIN cannot do that
// job here -- on a Pico W it hangs off the CYW43 over SPI, and in this firmware
// it is already the inter-Pico link heartbeat, ridden in the ping so both boards
// stay in step. D40 (green) is hard-wired +3V3 -> R40 -> GND and needs no code.
#define HB_PIN 15

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const float VBAT_V_PER_COUNT = 0.0049184f;

// ---------------------------------------------------------------- outputs
// ULN2803A ground-pulse outputs plus Q1's ceiling channel, same pins as
// hondaPico.ino. Active HIGH into the ULN input; the ULN sinks the car line to
// ground. Breadboard: GP17 -> ULN pin 2 (I2), output on ULN pin 17 (O2) --
// inputs count up 1..8 but outputs count DOWN, pin 11 = O8 ... pin 18 = O1,
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    }
  }

  // Inter-Pico heartbeat. The LED state rides IN the ping rather than each board
  // toggling its own, so the two LEDs are always in step instead of only being
  // locked to whatever phase they happened to start in. Toggling independently
  // meant the expansion node missing an odd number of pings while probing left
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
